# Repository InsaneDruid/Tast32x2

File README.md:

# Tast32x2 - a CBM2 to C64 keybboard adapter clone
The Tast32x2 is a 100% compatible clone of the the adapters used to connect a CBM2 Keyboard to the C64.
It implements all the features, including the ability to leave the original keyboard connected which can be usefull for the the interactive layout editor or when playing games that use a non-rom scanning routine.
Two Versions included to use in the LongBoard and Shortboard Versions of the C64.

[Schematic](https://github.com/InsaneDruid/Tast32x2/blob/main/Tast32x2.pdf "Schematic")  

[Bill of Materials](https://htmlpreview.github.io/?https://github.com/InsaneDruid/Tast32x2/blob/main/bom/Tast32x2_bom.html "Bill of Materials")

## The Firmware & Tools
There are two diskettes with tools and firmware floating around both can be used with the Tast32x2.
One also contains an editor that can be used to edit the key layout of the CBM2 keyboard.

## The License
This work is licensed under a Creative Commons Attribution-ShareAlike 4.0 International License.  
See https://creativecommons.org/licenses/by-sa/4.0/.

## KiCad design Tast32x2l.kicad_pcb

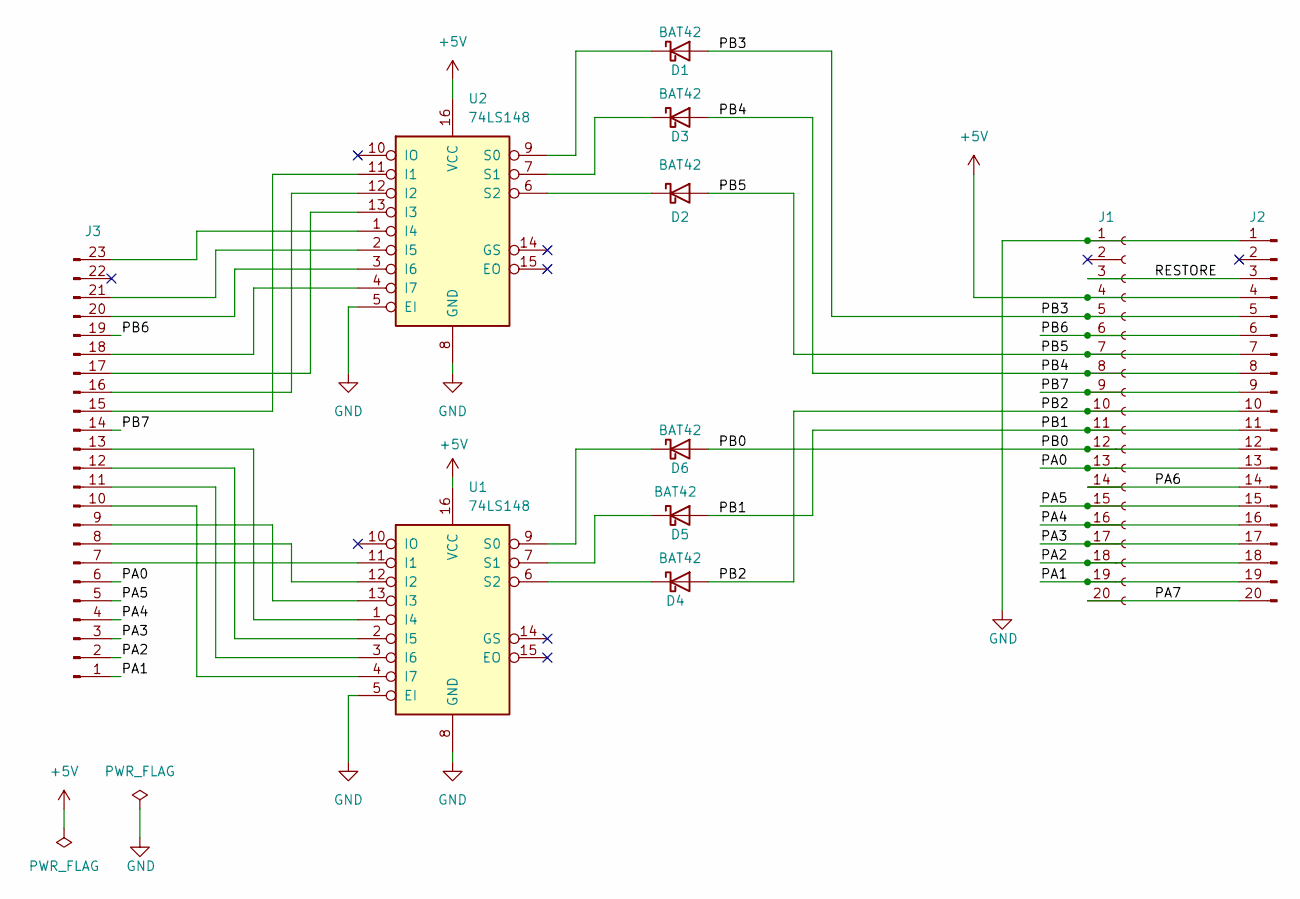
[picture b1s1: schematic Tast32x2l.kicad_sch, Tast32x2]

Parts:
D1, D2, D3, D4, D5, D6: BAT42; D_DO-35_SOD27_P7.62mm_Horizontal
J1: Conn_01x20_Female; PinSocket_1x20_P2.54mm_Vertical
J2: Conn_01x20_Male; PinHeader_1x20_P2.54mm_Vertical
J3: Conn_01x23_Male; PinHeader_1x23_P2.54mm_Vertical
U1, U2: 74LS148; DIP-16_W7.62mm

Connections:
+5V: J1.4, J2.4, U1.16 (VCC), U2.16 (VCC)
/PA0: J1.13, J2.13, J3.6
/PA1: J1.19, J2.19, J3.1
/PA2: J1.18, J2.18, J3.2
/PA3: J1.17, J2.17, J3.3
/PA4: J1.16, J2.16, J3.4
/PA5: J1.15, J2.15, J3.5
/PA6: J1.14, J2.14
/PA7: J1.20, J2.20
/PB0: D6.2 (A), J1.12, J2.12
/PB1: D5.2 (A), J1.11, J2.11
/PB2: D4.2 (A), J1.10, J2.10
/PB3: D1.2 (A), J1.5, J2.5
/PB4: D3.2 (A), J1.8, J2.8
/PB5: D2.2 (A), J1.7, J2.7
/PB6: J1.6, J2.6, J3.19
/PB7: J1.9, J2.9, J3.14
/RESTORE: J1.3, J2.3
GND: J1.1, J2.1, U1.5 (EI), U1.8 (GND), U2.5 (EI), U2.8 (GND)
unnamed: D1.1 (K), U2.9 (S0)
unnamed: D2.1 (K), U2.6 (S2)
unnamed: D3.1 (K), U2.7 (S1)
unnamed: D4.1 (K), U1.6 (S2)
unnamed: D5.1 (K), U1.7 (S1)
unnamed: D6.1 (K), U1.9 (S0)
unnamed: J3.7, U1.11 (I1)
unnamed: J3.8, U1.12 (I2)
unnamed: J3.9, U1.13 (I3)
unnamed: J3.10, U1.4 (I7)
unnamed: J3.11, U1.3 (I6)
unnamed: J3.12, U1.2 (I5)
unnamed: J3.13, U1.1 (I4)
unnamed: J3.15, U2.11 (I1)
unnamed: J3.16, U2.12 (I2)
unnamed: J3.17, U2.13 (I3)
unnamed: J3.18, U2.4 (I7)
unnamed: J3.20, U2.3 (I6)
unnamed: J3.21, U2.2 (I5)
unnamed: J3.23, U2.1 (I4)

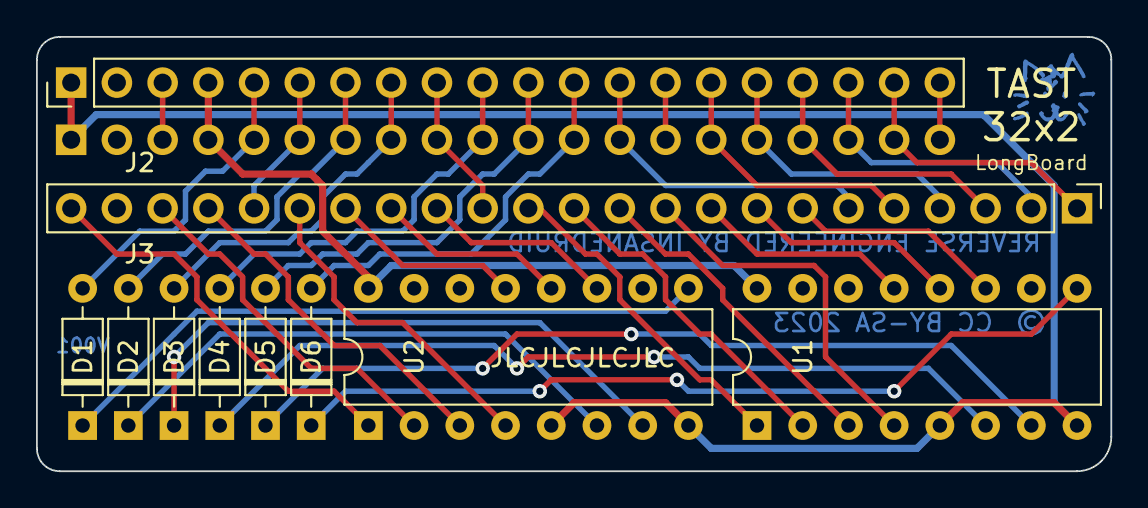
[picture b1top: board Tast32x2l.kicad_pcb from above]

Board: 2 copper layers, 59.7 x 24.1 mm, 11 parts (1 on the bottom side), 39 nets.

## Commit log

2024-02-16 kicad drawing sheet fixes
    fixed license links in drawing sheets to match board prints, readme and project

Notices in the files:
Tast32x2l.kicad_pcb:
License: CC BY-SA 4.0
CC BY-SA 2023
